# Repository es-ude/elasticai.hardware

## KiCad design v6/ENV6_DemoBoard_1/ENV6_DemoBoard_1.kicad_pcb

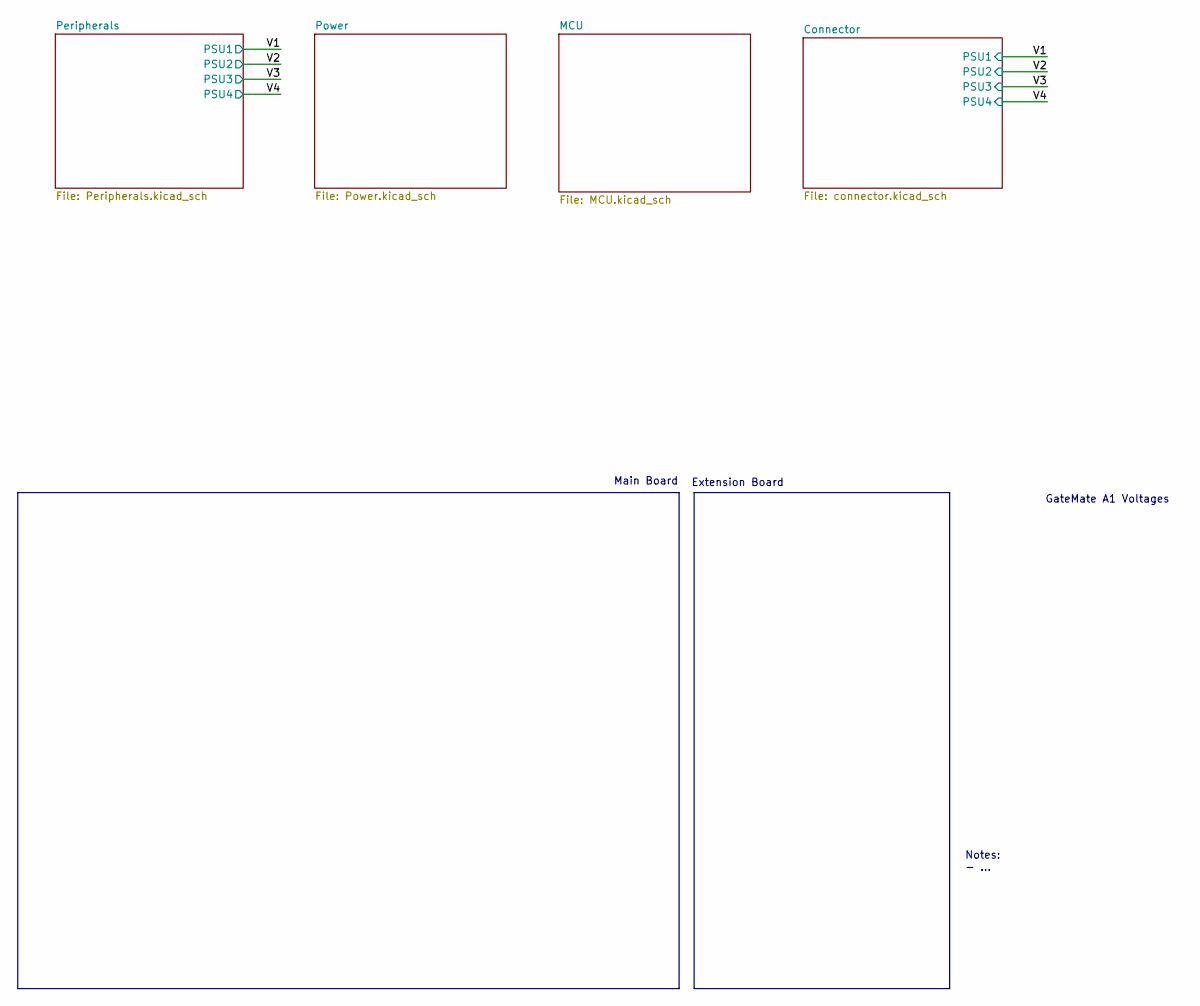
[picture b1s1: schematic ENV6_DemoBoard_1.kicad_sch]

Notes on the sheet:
Extension Board
Notes: - ...
Main Board
GateMate A1 Voltages

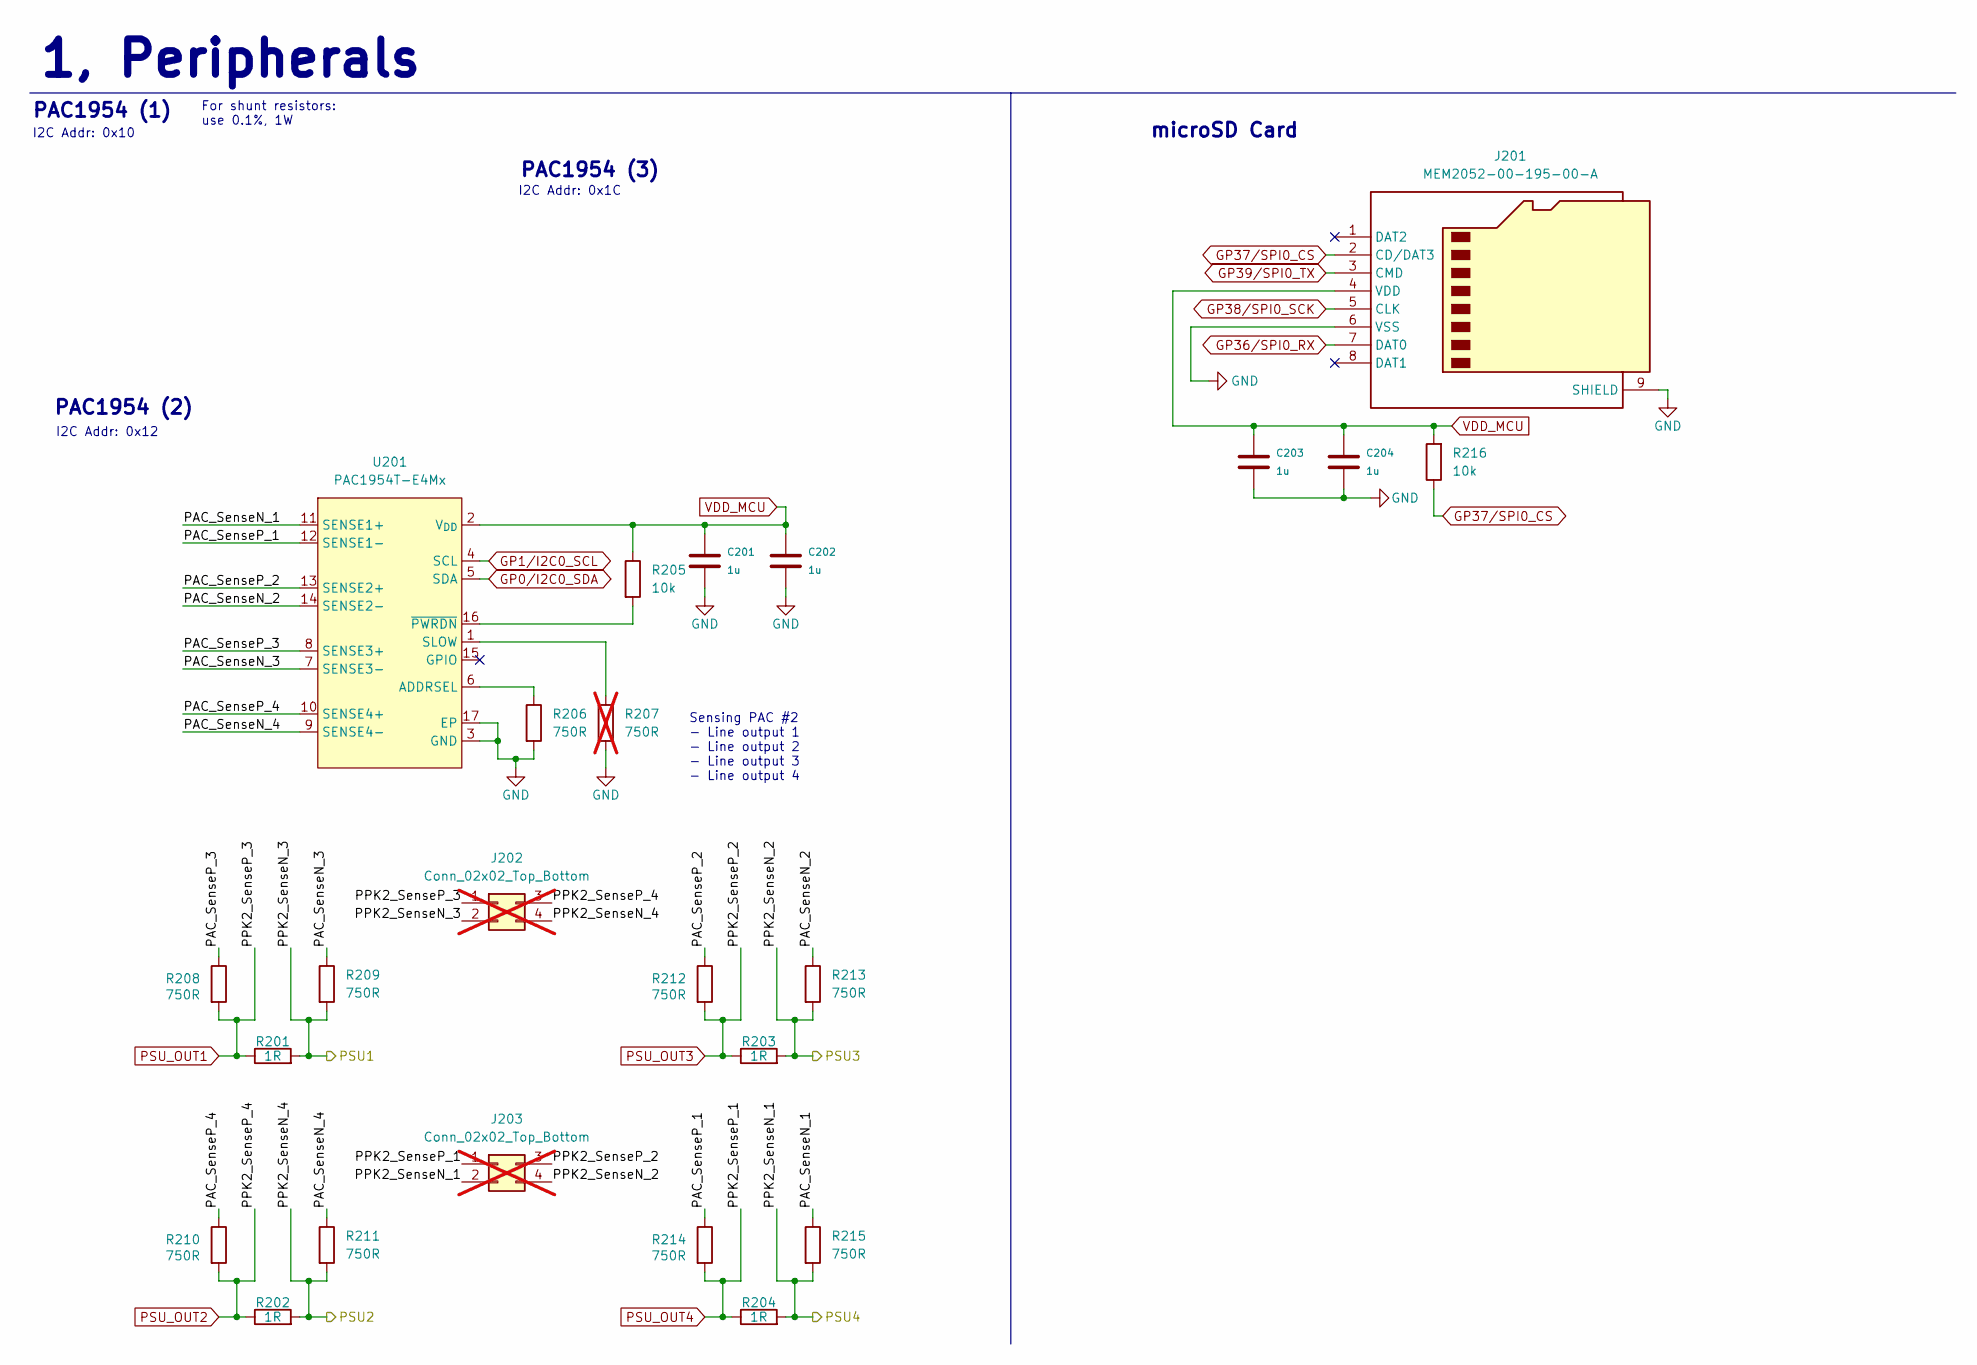
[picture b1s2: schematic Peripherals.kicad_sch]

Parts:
C201, C202, C203, C204: 1u; C_0402_1005Metric
J201: MEM2052-00-195-00-A; MEM20520019500A; Mouser Part Number 640-MEM20520019500A
J202, J203: Conn_02x02_Top_Bottom; PinHeader_2x02_P2.00mm_Vertical; not fitted
R201, R202, R203, R204: 1R; R_0603_1608Metric
R205, R216: 10k; R_0402_1005Metric
R206, R208, R209, R210, R211, R212, R213, R214, R215: 750R; R_0402_1005Metric
R207: 750R; R_0402_1005Metric; not fitted
U201: PAC1954T-E4Mx; VQFN-16-1EP_3x3mm_P0.5mm_EP1.1x1.1mm

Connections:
/Peripherals/PAC_SenseN_1: R215.1, U201.11 (SENSE1+)
/Peripherals/PAC_SenseN_2: R213.1, U201.14 (SENSE2-)
/Peripherals/PAC_SenseN_3: R209.1, U201.7 (SENSE3-)
/Peripherals/PAC_SenseN_4: R211.1, U201.9 (SENSE4-)
/Peripherals/PAC_SenseP_1: R214.1, U201.12 (SENSE1-)
/Peripherals/PAC_SenseP_2: R212.1, U201.13 (SENSE2+)
/Peripherals/PAC_SenseP_3: R208.1, U201.8 (SENSE3+)
/Peripherals/PAC_SenseP_4: R210.1, U201.10 (SENSE4+)
/V1: J202.2, R201.2, R209.2; also elsewhere on the board
/V2: J202.4, R202.2, R211.2; also elsewhere on the board
/V3: J203.4, R203.2, R213.2; also elsewhere on the board
/V4: J203.2, R204.2, R215.2; also elsewhere on the board
GND: C201.1, C202.1, C203.1, C204.1, J201.6 (VSS), J201.9 (SHIELD), J201.G1 (GND_1), J201.G2 (GND_2), J201.G3 (GND_3), J201.G4 (GND_4), R206.2, R207.2, U201.3 (GND), U201.17 (EP); also elsewhere on the board
GP0/I2C0_SDA: U201.5 (SDA); also elsewhere on the board
GP1/I2C0_SCL: U201.4 (SCL); also elsewhere on the board
GP36/SPI0_RX: J201.7 (DAT0); also elsewhere on the board
GP37/SPI0_CS: J201.2 (CD/DAT3), R216.1; also elsewhere on the board
GP38/SPI0_SCK: J201.5 (CLK); also elsewhere on the board
GP39/SPI0_TX: J201.3 (CMD); also elsewhere on the board
unnamed: R206.1, U201.6 (ADDRSEL)
unnamed: R207.1, U201.1 (SLOW)
unnamed: R205.2, U201.16 (~PWRDN)
PSU_OUT1: J202.1, R201.1, R208.2; also elsewhere on the board
PSU_OUT2: J202.3, R202.1, R210.2; also elsewhere on the board
PSU_OUT3: J203.3, R203.1, R212.2; also elsewhere on the board
PSU_OUT4: J203.1, R204.1, R214.2; also elsewhere on the board
VDD_MCU: C201.2, C202.2, C203.2, C204.2, J201.4 (VDD), R205.1, R216.2, U201.2 (V_{DD}); also elsewhere on the board

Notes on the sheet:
1, Peripherals
PAC1954 (1)
microSD Card
For shunt resistors: use 0.1%, 1W
I2C Addr: 0x1C
I2C Addr: 0x10
I2C Addr: 0x12
Sensing PAC #2 - Line output 1 - Line output 2 - Line output 3 - Line output 4
PAC1954 (2)
PAC1954 (3)

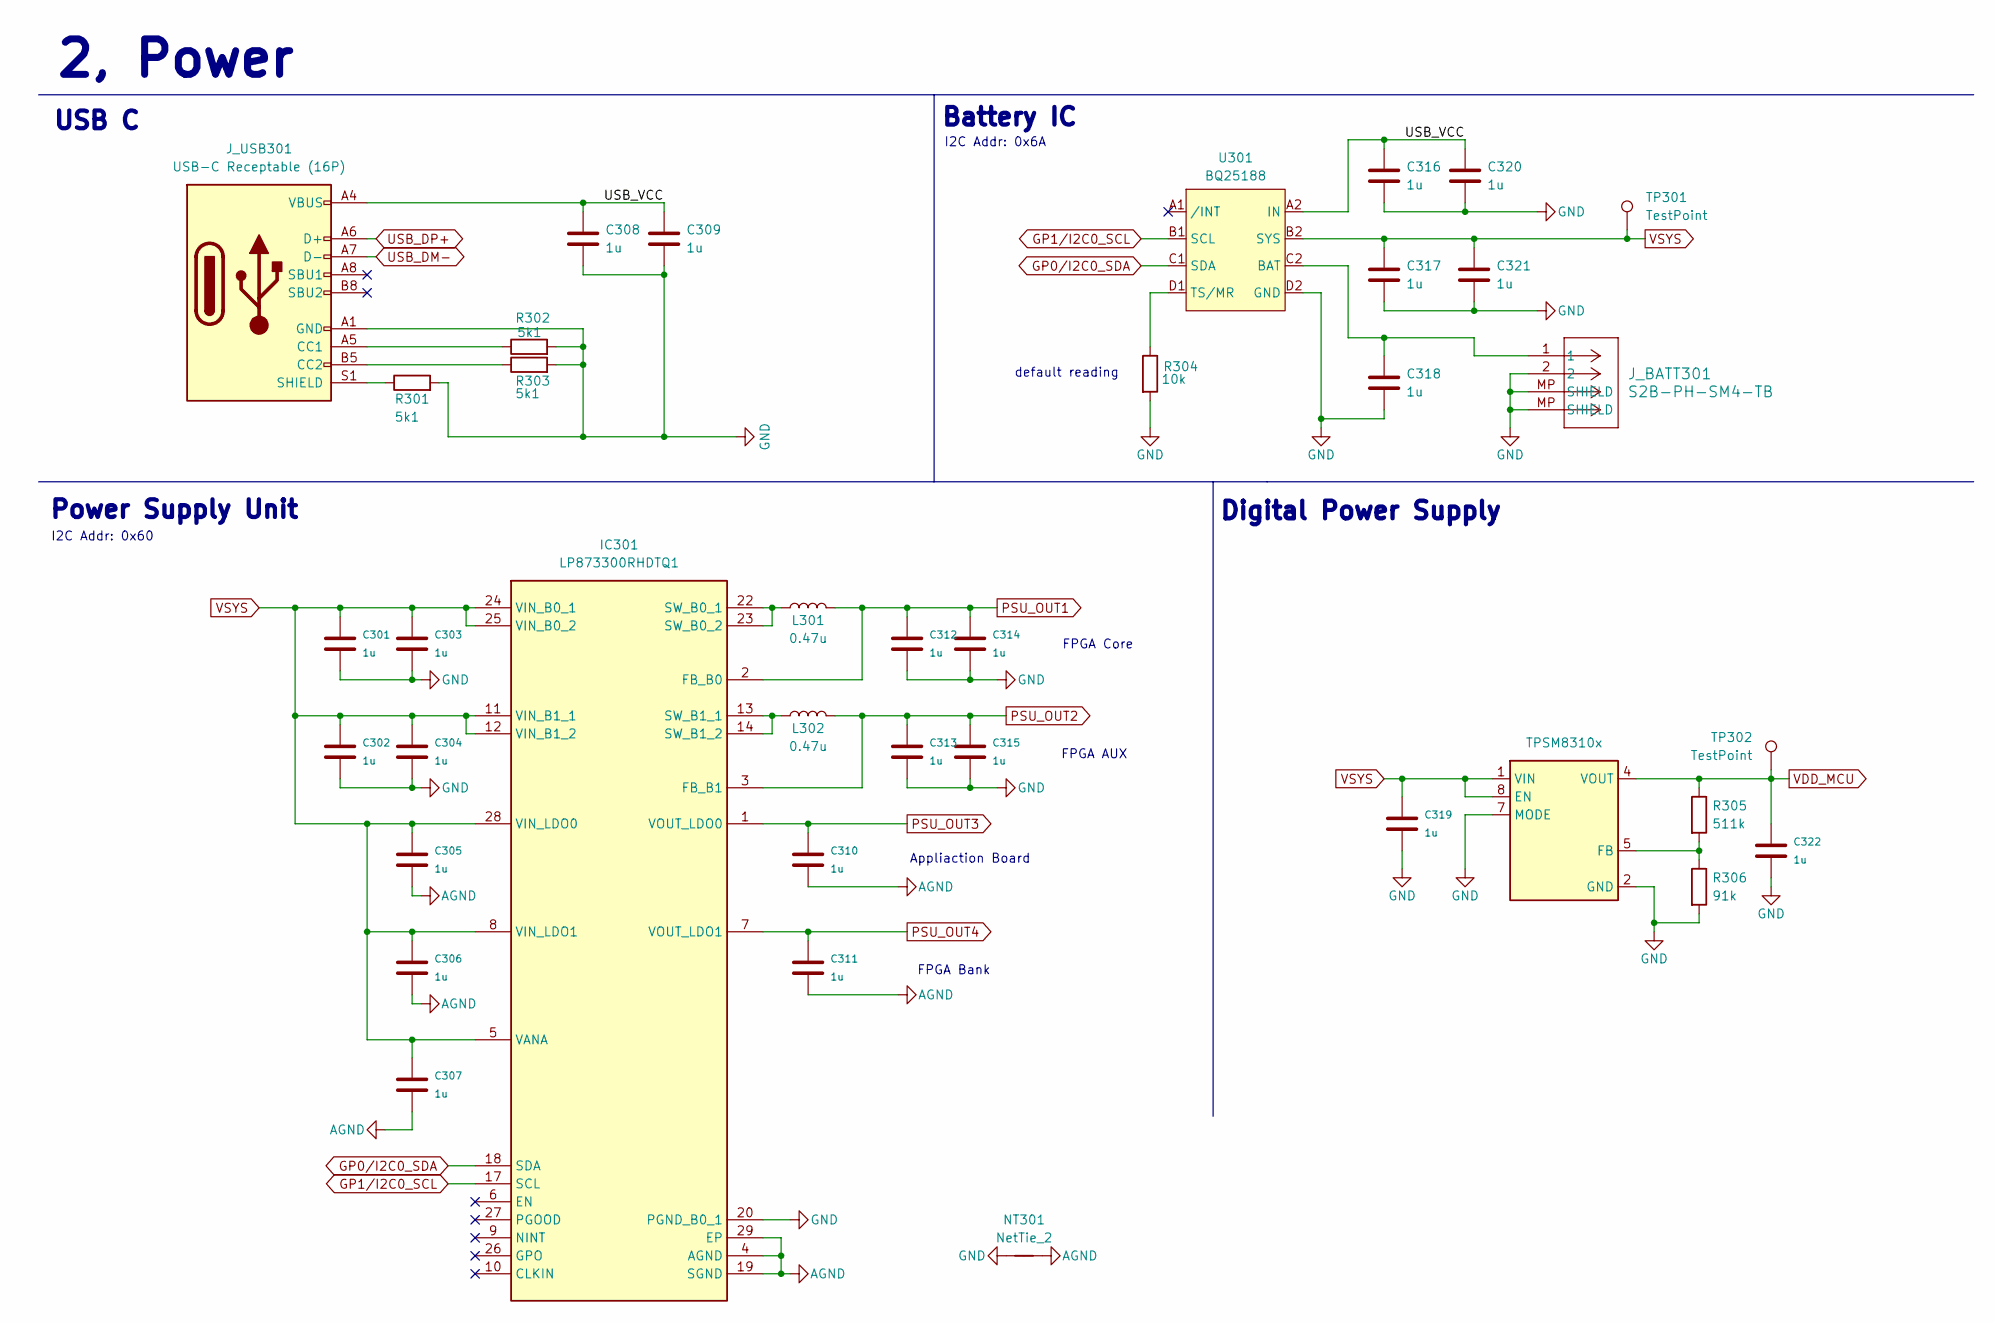
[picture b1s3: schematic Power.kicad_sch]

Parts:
C301, C302, C303, C304, C305, C306, C307, C308, C309, C310, C311, C312, C313, C314, C315, C316, C317, C318, C319, C320, C321, C322: 1u; C_0402_1005Metric
IC301: LP873300RHDTQ1; QFN50P500X500X80-29N; Mouser Part Number 595-LP873300RHDTQ1
J_BATT301: S2B-PH-SM4-TB; JST_PH_S2B-PH-SM4-TB_1x02-1MP_P2.00mm_Horizontal
J_USB301: USB-C Receptable (16P); USB_C_Receptacle_16P
L301, L302: 0.47u; L_1008_2520Metric
NT301: NetTie_2; NetTie-2_SMD_Pad0.5mm
R301, R302, R303: 5k1; R_0402_1005Metric
R304: 10k; R_0402_1005Metric
R305: 511k; R_0402_1005Metric
R306: 91k; R_0402_1005Metric
TP301, TP302: TestPoint; TestPoint_Pad_D1.0mm
U301: BQ25188; Texas_DSBGA-8_0.9x1.9mm_Layout2x4_P0.5mm
U302: TPSM8310x; MICROSIP8_SIU_TEX

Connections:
/Power/USB_VCC: C308.1, C309.1, C316.1, C320.1, J_USB301.A4 (VBUS), J_USB301.A9 (VBUS), J_USB301.B4 (VBUS), J_USB301.B9 (VBUS), U301.A2 (IN)
AGND: C305.1, C306.1, C307.1, C310.1, C311.1, IC301.4 (AGND), IC301.19 (SGND), IC301.29 (EP), NT301.2
GND: C301.1, C302.1, C303.1, C304.1, C308.2, C309.2, C312.1, C313.1, C314.1, C315.1, C316.2, C317.2, C318.2, C319.1, C320.2, C321.2, C322.1, IC301.15 (PGND_B1_1), IC301.16 (PGND_B1_2), IC301.20 (PGND_B0_1), IC301.21 (PGND_B0_2), J_BATT301.2, J_BATT301.MP (SHIELD), J_USB301.A1 (GND), J_USB301.A12 (GND), J_USB301.B1 (GND), J_USB301.B12 (GND), NT301.1, R301.2, R302.2, R303.2, R304.2, R306.2, U301.D2 (GND), U302.2 (GND), U302.3 (GND), U302.6 (GND), U302.7 (MODE); also elsewhere on the board
GP0/I2C0_SDA: IC301.18 (SDA), U301.C1 (SDA); also elsewhere on the board
GP1/I2C0_SCL: IC301.17 (SCL), U301.B1 (SCL); also elsewhere on the board
unnamed: IC301.22 (SW_B0_1), IC301.23 (SW_B0_2), L301.1
unnamed: IC301.13 (SW_B1_1), IC301.14 (SW_B1_2), L302.1
unnamed: J_USB301.A5 (CC1), R302.1
unnamed: J_USB301.B5 (CC2), R303.1
unnamed: J_USB301.S1 (SHIELD), R301.1
unnamed: C318.1, J_BATT301.1, U301.C2 (BAT)
unnamed: R304.1, U301.D1 (TS/MR)
unnamed: R305.2, R306.1, U302.5 (FB)
PSU_OUT1: C312.2, C314.2, IC301.2 (FB_B0), L301.2; also elsewhere on the board
PSU_OUT2: C313.2, C315.2, IC301.3 (FB_B1), L302.2; also elsewhere on the board
PSU_OUT3: C310.2, IC301.1 (VOUT_LDO0); also elsewhere on the board
PSU_OUT4: C311.2, IC301.7 (VOUT_LDO1); also elsewhere on the board
USB_DM-: J_USB301.A7 (D-), J_USB301.B7 (D-); also elsewhere on the board
USB_DP+: J_USB301.A6 (D+), J_USB301.B6 (D+); also elsewhere on the board
VDD_MCU: C322.2, R305.1, TP302.1 (1_1), U302.4 (VOUT); also elsewhere on the board
VSYS: C301.2, C302.2, C303.2, C304.2, C305.2, C306.2, C307.2, C317.1, C319.2, C321.1, IC301.5 (VANA), IC301.8 (VIN_LDO1), IC301.11 (VIN_B1_1), IC301.12 (VIN_B1_2), IC301.24 (VIN_B0_1), IC301.25 (VIN_B0_2), IC301.28 (VIN_LDO0), TP301.1 (1_1), U301.B2 (SYS), U302.1 (VIN), U302.8 (EN); also elsewhere on the board

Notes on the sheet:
Battery IC
FPGA Bank
I2C Addr: 0x6A
default reading
USB C
2, Power
FPGA Core
Power Supply Unit
FPGA AUX
I2C Addr: 0x60
Digital Power Supply
Appliaction Board

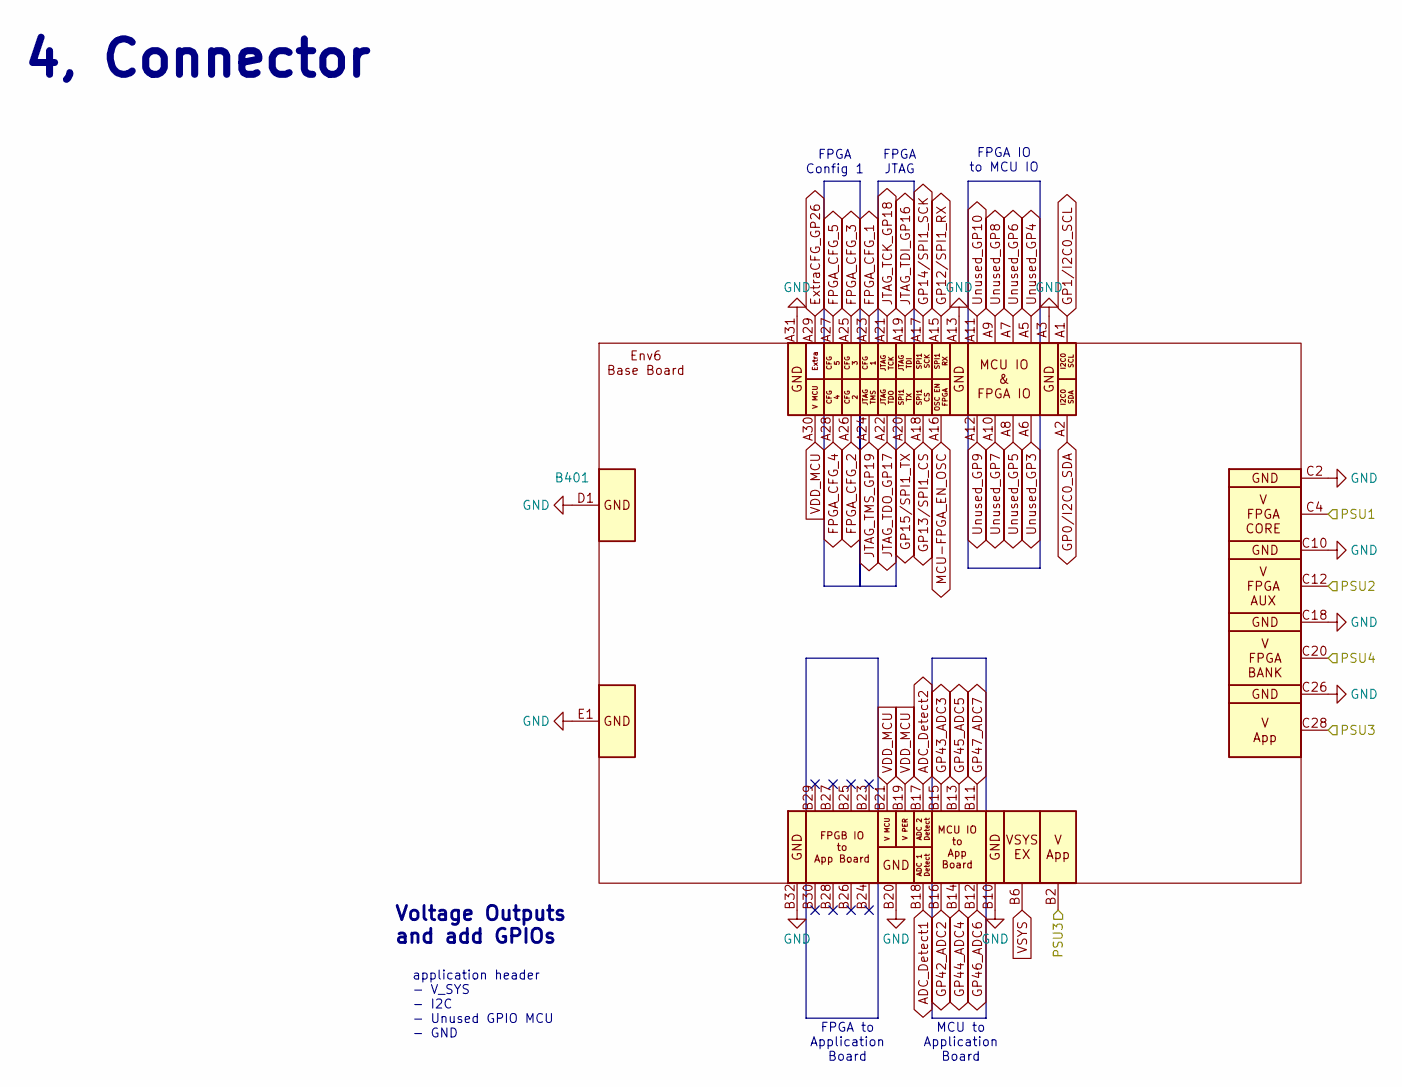
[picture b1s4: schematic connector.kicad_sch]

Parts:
B401: BaseBoard_ENv6

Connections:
/V1: B401.C3, B401.C4, B401.C5, B401.C6, B401.C7, B401.C8; also elsewhere on the board
/V2: B401.C11, B401.C12, B401.C13, B401.C14, B401.C15, B401.C16; also elsewhere on the board
/V3: B401.B1, B401.B2, B401.B3, B401.B4, B401.C27, B401.C28, B401.C29, B401.C30, B401.C31, B401.C32; also elsewhere on the board
/V4: B401.C19, B401.C20, B401.C21, B401.C22, B401.C23, B401.C24; also elsewhere on the board
ADC_Detect1: B401.B18; also elsewhere on the board
ADC_Detect2: B401.B17; also elsewhere on the board
ExtraCFG_GP26: B401.A29; also elsewhere on the board
FPGA_CFG_1: B401.A23; also elsewhere on the board
FPGA_CFG_2: B401.A26; also elsewhere on the board
FPGA_CFG_3: B401.A25; also elsewhere on the board
FPGA_CFG_4: B401.A28; also elsewhere on the board
FPGA_CFG_5: B401.A27; also elsewhere on the board
GND: B401.A3, B401.A4, B401.A13, B401.A14, B401.A31, B401.A32, B401.B9, B401.B10, B401.B20, B401.B22, B401.B31, B401.B32, B401.C1, B401.C2, B401.C9, B401.C10, B401.C17, B401.C18, B401.C25, B401.C26, B401.D1, B401.D2, B401.D3, B401.D4, B401.D5, B401.D6, B401.D7, B401.D8, B401.E1, B401.E2, B401.E3, B401.E4, B401.E5, B401.E6, B401.E7, B401.E8; also elsewhere on the board
GP0/I2C0_SDA: B401.A2; also elsewhere on the board
GP1/I2C0_SCL: B401.A1; also elsewhere on the board
GP12/SPI1_RX: B401.A15; also elsewhere on the board
GP13/SPI1_CS: B401.A18; also elsewhere on the board
GP14/SPI1_SCK: B401.A17; also elsewhere on the board
GP15/SPI1_TX: B401.A20; also elsewhere on the board
GP42_ADC2: B401.B16; also elsewhere on the board
GP43_ADC3: B401.B15; also elsewhere on the board
GP44_ADC4: B401.B14; also elsewhere on the board
GP45_ADC5: B401.B13; also elsewhere on the board
GP46_ADC6: B401.B12; also elsewhere on the board
GP47_ADC7: B401.B11; also elsewhere on the board
JTAG_TCK_GP18: B401.A21; also elsewhere on the board
JTAG_TDI_GP16: B401.A19; also elsewhere on the board
JTAG_TDO_GP17: B401.A22; also elsewhere on the board
JTAG_TMS_GP19: B401.A24; also elsewhere on the board
MCU-FPGA_EN_OSC: B401.A16; also elsewhere on the board
Unused_GP3: B401.A6; also elsewhere on the board
Unused_GP4: B401.A5; also elsewhere on the board
Unused_GP5: B401.A8; also elsewhere on the board
Unused_GP6: B401.A7; also elsewhere on the board
Unused_GP7: B401.A10; also elsewhere on the board
Unused_GP8: B401.A9; also elsewhere on the board
Unused_GP9: B401.A12; also elsewhere on the board
Unused_GP10: B401.A11; also elsewhere on the board
VDD_MCU: B401.A30, B401.B19, B401.B21; also elsewhere on the board
VSYS: B401.B5, B401.B6, B401.B7, B401.B8; also elsewhere on the board

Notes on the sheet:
FPGA JTAG
FPGA IO to MCU IO
FPGA to Application Board
MCU to Application Board
4, Connector
FPGA Config 1
application header - V_SYS - I2C - Unused GPIO MCU - GND
Voltage Outputs and add GPIOs

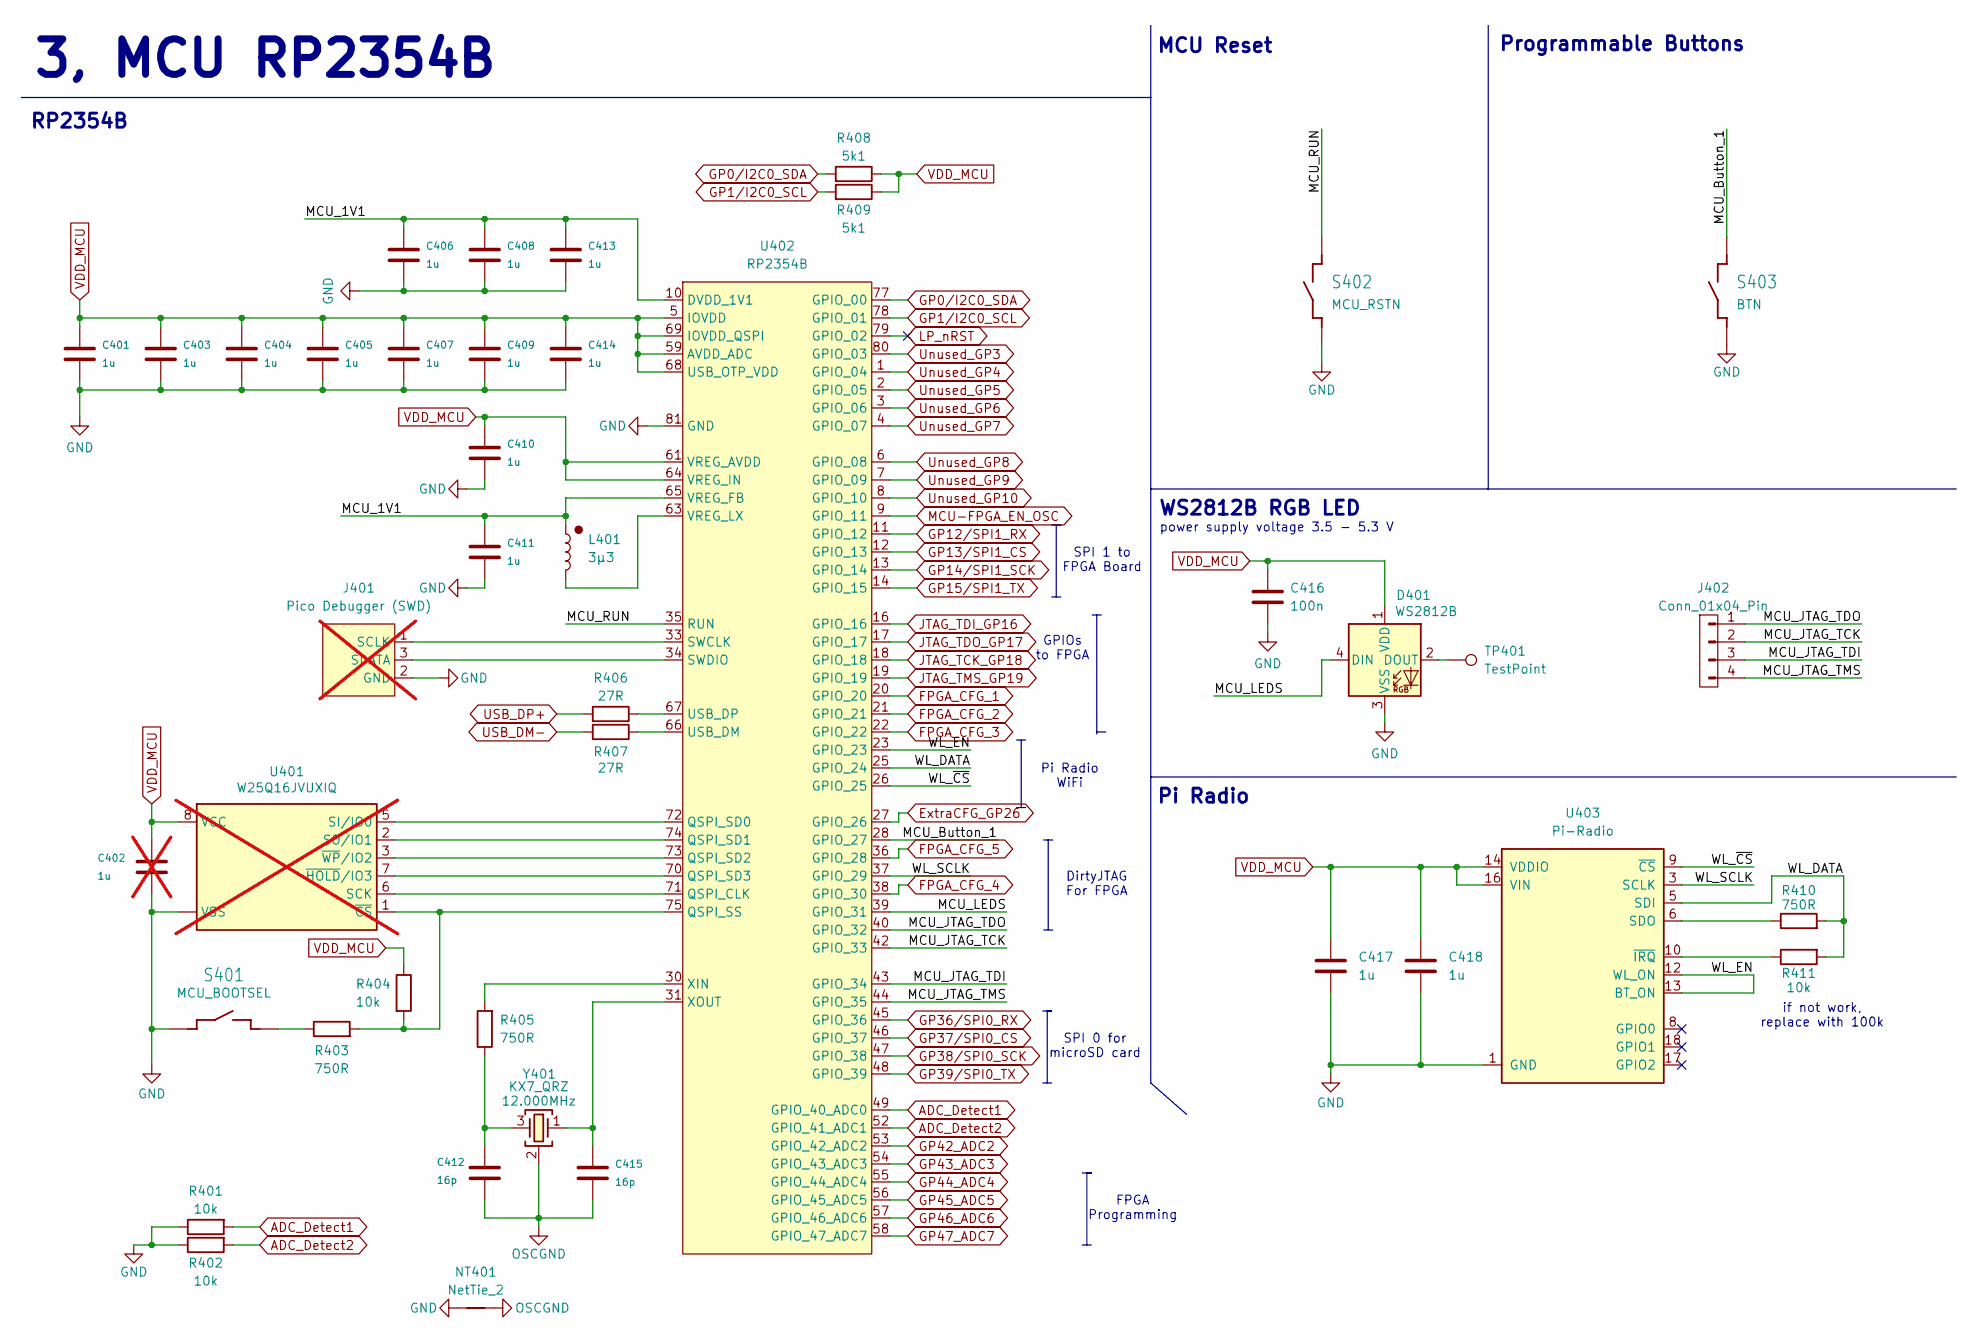
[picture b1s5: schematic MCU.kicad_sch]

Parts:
C401, C403, C404, C405, C406, C407, C408, C409, C410, C411, C413, C414, C417, C418: 1u; C_0402_1005Metric
C402: 1u; C_0402_1005Metric; not fitted
C412, C415: 16p; C_0402_1005Metric
C416: 100n; C_0402_1005Metric
D401: WS2812B; LED_WS2812B_PLCC4_5.0x5.0mm_P3.2mm
J401: Pico Debugger (SWD); PinHeader_1x03_P2.00mm_Vertical; not fitted
J402: Conn_01x04_Pin; PinSocket_1x04_P2.00mm_Vertical
L401: 3µ3; L_0805_2012_metric_Alligned_HandSolder
NT401: NetTie_2; NetTie-2_SMD_Pad0.5mm
R401, R402, R404, R411: 10k; R_0402_1005Metric
R403, R405, R410: 750R; R_0402_1005Metric
R406, R407: 27R; R_0402_1005Metric
R408, R409: 5k1; R_0402_1005Metric
S401: MCU_BOOTSEL; TACTILE-SWITCH
S402: MCU_RSTN; TACTILE-SWITCH
S403: BTN; TACTILE-SWITCH
TP401: TestPoint; TestPoint_Pad_D1.0mm
U401: W25Q16JVUXIQ; USON-8-1EP_3x2mm_P0.5mm_EP0.2x1.6mm; not fitted
U402: RP2354B; QFN-80_EP_10x10_Pitch0.4mm
U403: Pi-Radio; RPi-Radio-Module
Y401: KX7_QRZ; KX-7; MPN ABM8G-25.000MHZ-18-D2Y-T3

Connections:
/MCU/MCU_1V1: C406.2, C408.2, C411.2, C413.2, L401.1, U402.10 (DVDD_1V1), U402.32 (DVDD_1V1), U402.51 (DVDD_1V1), U402.65 (VREG_FB)
/MCU/MCU_Button_1: S403.3 (2), S403.4 (2), U402.28 (GPIO_27)
/MCU/MCU_JTAG_TCK: J402.2, U402.42 (GPIO_33)
/MCU/MCU_JTAG_TDI: J402.3, U402.43 (GPIO_34)
/MCU/MCU_JTAG_TDO: J402.1, U402.40 (GPIO_32)
/MCU/MCU_JTAG_TMS: J402.4, U402.44 (GPIO_35)
/MCU/MCU_LEDS: D401.4 (DIN), U402.39 (GPIO_31)
/MCU/MCU_RUN: S402.3 (2), S402.4 (2), U402.35 (RUN)
/MCU/WL_DATA: R410.2, R411.2, U402.25 (GPIO_24), U403.5 (SDI)
/MCU/WL_EN: U402.23 (GPIO_23), U403.12 (WL_ON), U403.13 (BT_ON)
/MCU/WL_SCLK: U402.37 (GPIO_29), U403.3 (SCLK)
/MCU/WL_~CS: U402.26 (GPIO_25), U403.9 (~CS)
ADC_Detect1: R401.2, U402.49 (GPIO_40_ADC0); also elsewhere on the board
ADC_Detect2: R402.2, U402.52 (GPIO_41_ADC1); also elsewhere on the board
ExtraCFG_GP26: U402.27 (GPIO_26); also elsewhere on the board
FPGA_CFG_1: U402.20 (GPIO_20); also elsewhere on the board
FPGA_CFG_2: U402.21 (GPIO_21); also elsewhere on the board
FPGA_CFG_3: U402.22 (GPIO_22); also elsewhere on the board
FPGA_CFG_4: U402.38 (GPIO_30); also elsewhere on the board
FPGA_CFG_5: U402.36 (GPIO_28); also elsewhere on the board
GND: C401.1, C402.2, C403.1, C404.1, C405.1, C406.1, C407.1, C408.1, C409.1, C410.1, C411.1, C413.1, C414.1, C416.2, C417.2, C418.2, D401.3 (VSS), J401.2 (GND), NT401.1, R401.1, R402.1, S401.1, S401.2 (1), S402.1, S402.2 (1), S403.1, S403.2 (1), U401.4 (VSS), U401.9 (VSS), U402.62 (GND), U402.81 (GND), U403.1 (GND), U403.4 (GND), U403.7 (GND), U403.11 (GND), U403.15 (GND), U403.21 (GND); also elsewhere on the board
GP0/I2C0_SDA: R408.2, U402.77 (GPIO_00); also elsewhere on the board
GP1/I2C0_SCL: R409.2, U402.78 (GPIO_01); also elsewhere on the board
GP12/SPI1_RX: U402.11 (GPIO_12); also elsewhere on the board
GP13/SPI1_CS: U402.12 (GPIO_13); also elsewhere on the board
GP14/SPI1_SCK: U402.13 (GPIO_14); also elsewhere on the board
GP15/SPI1_TX: U402.14 (GPIO_15); also elsewhere on the board
GP36/SPI0_RX: U402.45 (GPIO_36); also elsewhere on the board
GP37/SPI0_CS: U402.46 (GPIO_37); also elsewhere on the board
GP38/SPI0_SCK: U402.47 (GPIO_38); also elsewhere on the board
GP39/SPI0_TX: U402.48 (GPIO_39); also elsewhere on the board
GP42_ADC2: U402.53 (GPIO_42_ADC2); also elsewhere on the board
GP43_ADC3: U402.54 (GPIO_43_ADC3); also elsewhere on the board
GP44_ADC4: U402.55 (GPIO_44_ADC4); also elsewhere on the board
GP45_ADC5: U402.56 (GPIO_45_ADC5); also elsewhere on the board
GP46_ADC6: U402.57 (GPIO_46_ADC6); also elsewhere on the board
GP47_ADC7: U402.58 (GPIO_47_ADC7); also elsewhere on the board
JTAG_TCK_GP18: U402.18 (GPIO_18); also elsewhere on the board
JTAG_TDI_GP16: U402.16 (GPIO_16); also elsewhere on the board
JTAG_TDO_GP17: U402.17 (GPIO_17); also elsewhere on the board
JTAG_TMS_GP19: U402.19 (GPIO_19); also elsewhere on the board
LP_nRST: U402.79 (GPIO_02)
MCU-FPGA_EN_OSC: U402.9 (GPIO_11); also elsewhere on the board
unnamed: C412.2, R405.1, Y401.3
unnamed: D401.2 (DOUT), TP401.1 (1_1)
unnamed: J401.1 (SCLK), U402.33 (SWCLK)
unnamed: J401.3 (SDATA), U402.34 (SWDIO)
unnamed: R403.1, S401.3 (2), S401.4 (2)
unnamed: U401.6 (SCK), U402.71 (QSPI_CLK)
unnamed: U401.5 (SI/IO0), U402.72 (QSPI_SD0)
unnamed: U401.2 (SO/IO1), U402.74 (QSPI_SD1)
unnamed: R403.2, R404.2, U401.1 (~CS), U402.75 (QSPI_SS)
unnamed: U401.7 (~HOLD/IO3), U402.70 (QSPI_SD3)
unnamed: U401.3 (~WP/IO2), U402.73 (QSPI_SD2)
unnamed: R407.1, U402.66 (USB_DM)
unnamed: R406.1, U402.67 (USB_DP)
unnamed: L401.2, U402.63 (VREG_LX)
unnamed: R405.2, U402.30 (XIN)
unnamed: C415.2, U402.31 (XOUT), Y401.1
unnamed: R410.1, U403.6 (SDO)
unnamed: R411.1, U403.10 (~IRQ)
OSCGND: C412.1, C415.1, NT401.2, Y401.2 (SH), Y401.4 (SH)
USB_DM-: R407.2; also elsewhere on the board
USB_DP+: R406.2; also elsewhere on the board
Unused_GP3: U402.80 (GPIO_03); also elsewhere on the board
Unused_GP4: U402.1 (GPIO_04); also elsewhere on the board
Unused_GP5: U402.2 (GPIO_05); also elsewhere on the board
Unused_GP6: U402.3 (GPIO_06); also elsewhere on the board
Unused_GP7: U402.4 (GPIO_07); also elsewhere on the board
Unused_GP8: U402.6 (GPIO_08); also elsewhere on the board
Unused_GP9: U402.7 (GPIO_09); also elsewhere on the board
Unused_GP10: U402.8 (GPIO_10); also elsewhere on the board
VDD_MCU: C401.2, C402.1, C403.2, C404.2, C405.2, C407.2, C409.2, C410.2, C414.2, C416.1, C417.1, C418.1, D401.1 (VDD), R404.1, R408.1, R409.1, U401.8 (VCC), U402.5 (IOVDD), U402.15 (IOVDD), U402.24 (IOVDD), U402.29 (IOVDD), U402.41 (IOVDD), U402.50 (IOVDD), U402.59 (AVDD_ADC), U402.60 (IOVDD), U402.61 (VREG_AVDD), U402.64 (VREG_IN), U402.68 (USB_OTP_VDD), U402.69 (IOVDD_QSPI), U402.76 (IOVDD), U403.14 (VDDIO), U403.16 (VIN); also elsewhere on the board

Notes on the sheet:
SPI 0 for microSD card
FPGA Programming
Programmable Buttons
GPIOs to FPGA
Pi Radio WiFi
Pi Radio
if not work, replace with 100k
RP2354B
SPI 1 to FPGA Board
3, MCU RP2354B
DirtyJTAG For FPGA
power supply voltage 3.5 - 5.3 V
WS2812B RGB LED
MCU Reset

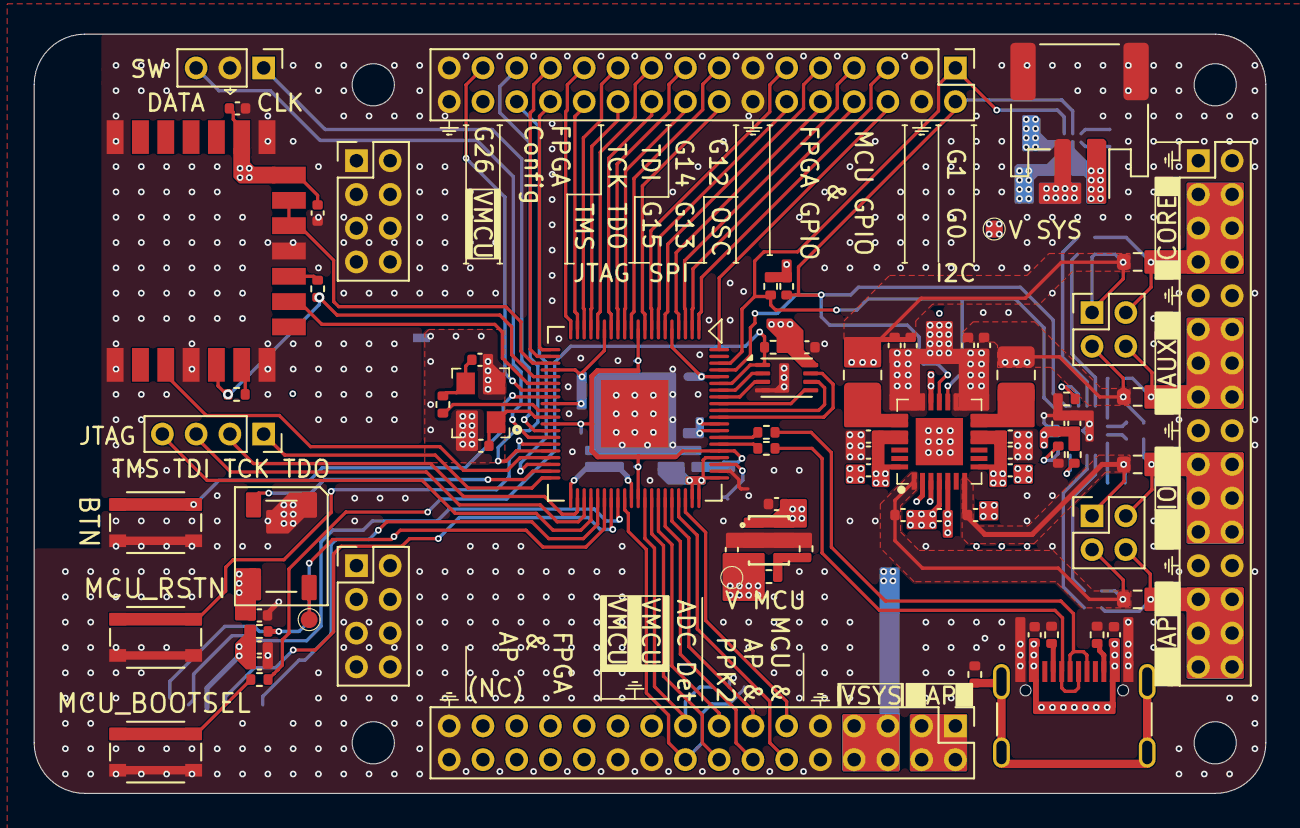
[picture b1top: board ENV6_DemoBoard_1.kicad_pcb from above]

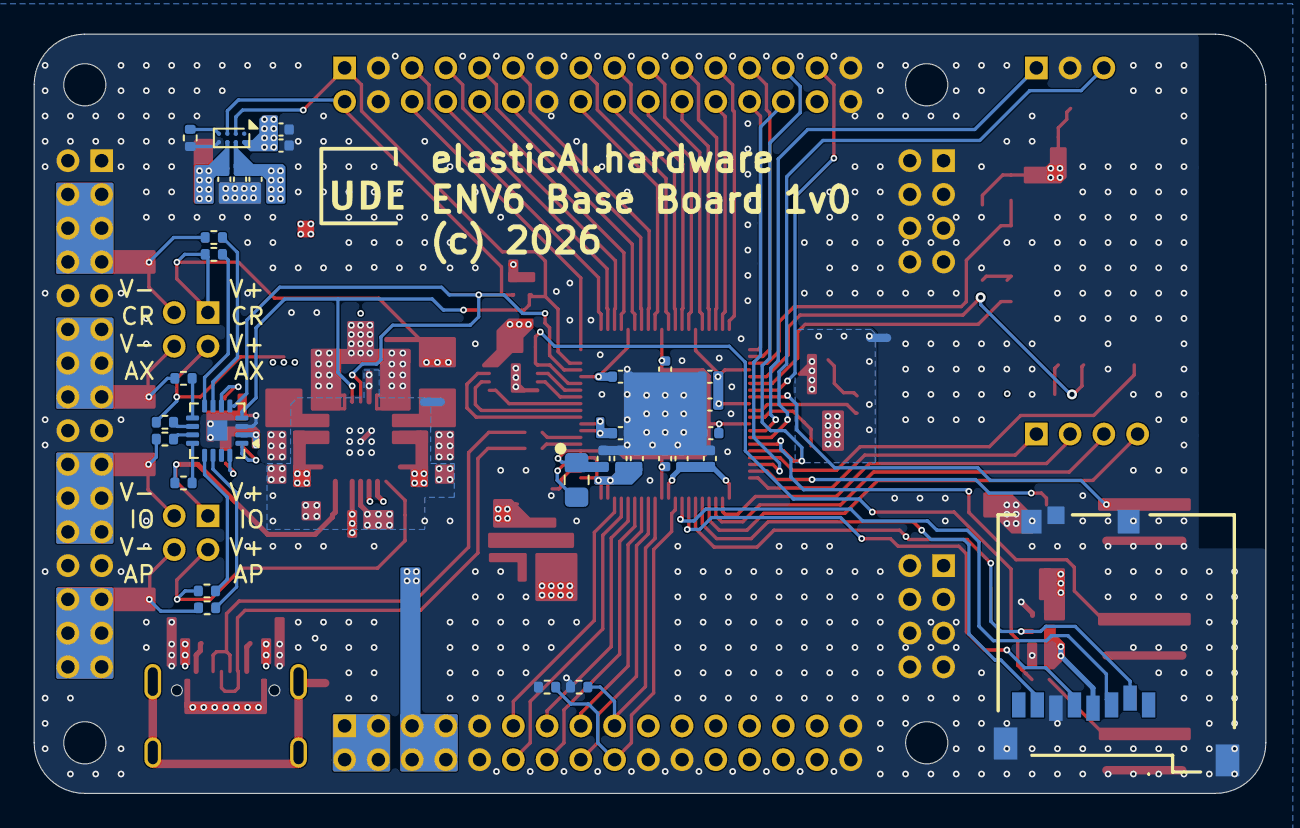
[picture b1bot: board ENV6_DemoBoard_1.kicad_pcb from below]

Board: 4 copper layers, 73.0 x 45.0 mm, 105 parts (34 on the bottom side), 102 nets.

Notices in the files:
v6/ENV6_DemoBoard_1/ENV6_DemoBoard_1.kicad_pcb:
(c) 2026
parts and their libraries:
License: Apache-2.0
